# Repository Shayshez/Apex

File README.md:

# Apex
## CC-BY-SA 4.0
Rotatable Envelope/LFO/tap LFO/Drum generator, Based on MI "Peaks"

## ROTATABLE = Modules for 3u / 1u
Apex comes with 2 panels: 1u/20hp and 3u/6hp

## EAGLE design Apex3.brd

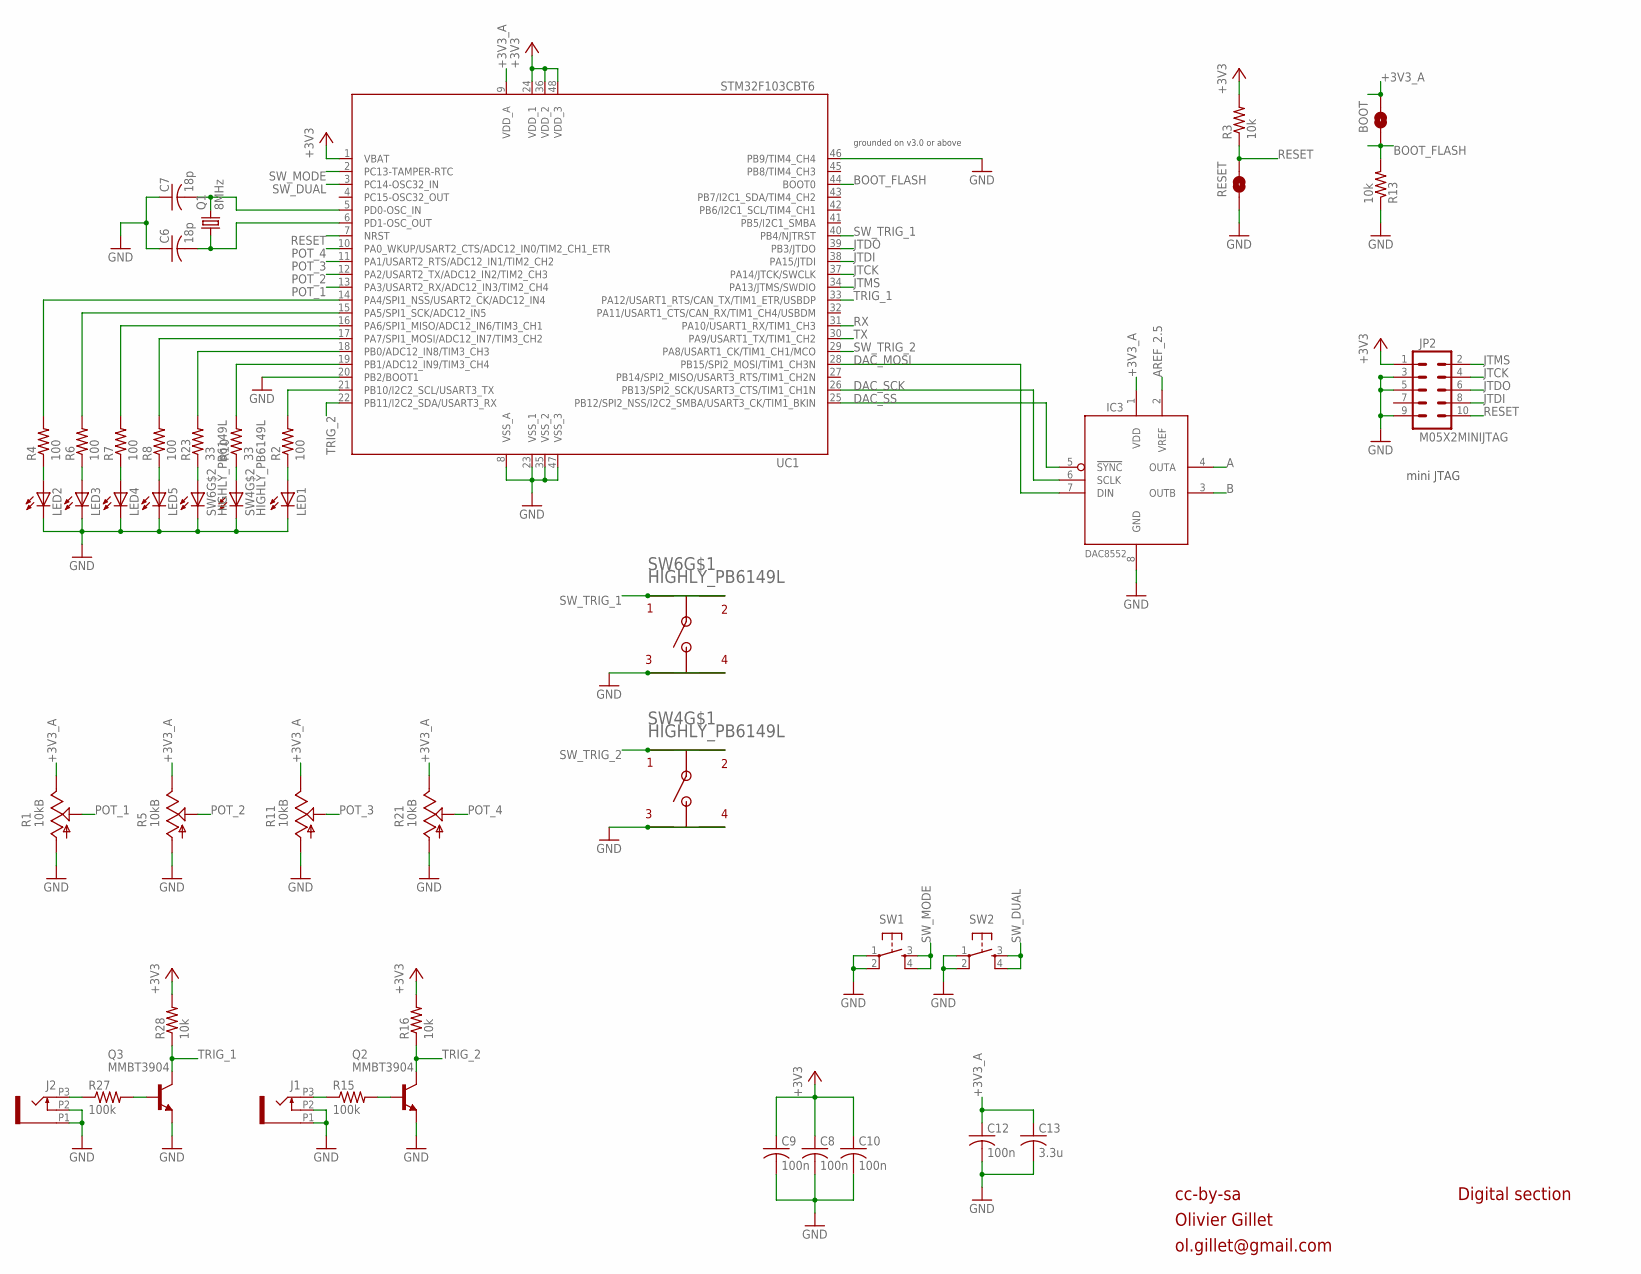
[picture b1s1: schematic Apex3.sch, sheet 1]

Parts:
BOOT: BOOT; SMT-JUMPER_2_NO_SILK
C6, C7: 18p; C0603
C8, C9, C10, C12: 100n; C0603
C13: 3.3u; C0603
IC3: DAC8552; MSOP-8
J1, J2: OG-PJ301_PJ301_THONKICONN; OG-PJ301_WQP_PJ_301M6_NO_HOLE
JP2: M05X2MINIJTAG; 2X5-1.27
LED1, LED2, LED3, LED4, LED5: LED3MM
Q1: 8MHz; HC49UP
Q2, Q3: MMBT3904; SOT23-BEC
R1, R5, R11, R21: 10kB; POT-ALPS_ALPS_POT_VERTICAL
R2, R4, R6, R7, R8: 100; R0603
R3, R13, R16, R28: 10k; R0603
R10, R23: 33; R0603
R15, R27: 100k; R0603
RESET: RESET; SMT-JUMPER_2_NO_SILK
SW1, SW2: TAC_SWITCHPTH; TACTILE-PTH
SW4, SW6: HIGHLY_PB6149L; HIGHLY_PB64149L
UC1: STM32F103CBT6; LQFP48

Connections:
+3V3: C8.1, C9.1, C10.1, JP2.1, R3.2, R16.2, R28.2, UC1.1 (VBAT), UC1.24 (VDD_1), UC1.36 (VDD_2), UC1.48 (VDD_3); also elsewhere on the board
+3V3_A: BOOT.2, C12.1, C13.1, IC3.1 (VDD), R1.P$1 (E), R5.P$1 (E), R11.P$1 (E), R21.P$1 (E), UC1.9 (VDD_A); also elsewhere on the board
A: IC3.4 (OUTA); also elsewhere on the board
AREF_2.5: IC3.2 (VREF); also elsewhere on the board
B: IC3.3 (OUTB); also elsewhere on the board
BOOT_FLASH: BOOT.1, R13.2, UC1.44 (BOOT0)
DAC_MOSI: IC3.7 (DIN), UC1.28 (PB15/SPI2_MOSI/TIM1_CH3N)
DAC_SCK: IC3.6 (SCLK), UC1.26 (PB13/SPI2_SCK/USART3_CTS/TIM1_CH1N)
DAC_SS: IC3.5 (!SYNC), UC1.25 (PB12/SPI2_NSS/I2C2_SMBA/USART3_CK/TIM1_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)
GND: C6.1, C7.1, C8.2, C9.2, C10.2, C12.2, C13.2, IC3.8 (GND), J1.P1 (1), J1.P2 (2), J2.P1 (1), J2.P2 (2), JP2.3, JP2.5, JP2.9, LED1.K (C), LED2.K (C), LED3.K (C), LED4.K (C), LED5.K (C), Q2.E, Q3.E, R1.P$3 (A), R5.P$3 (A), R11.P$3 (A), R13.1, R21.P$3 (A), RESET.1, SW1.1, SW1.2, SW2.1, SW2.2, SW4.L2, SW4.P$3, SW4.P$4, SW6.L2, SW6.P$3, SW6.P$4, UC1.8 (VSS_A), UC1.20 (PB2/BOOT1), UC1.23 (VSS_1), UC1.35 (VSS_2), UC1.46 (PB9/TIM4_CH4), UC1.47 (VSS_3); also elsewhere on the board
JTCK: JP2.4, UC1.37 (PA14/JTCK/SWCLK)
JTDI: JP2.8, UC1.38 (PA15/JTDI)
JTDO: JP2.6, UC1.39 (PB3/JTDO)
JTMS: JP2.2, UC1.34 (PA13/JTMS/SWDIO)
unnamed: J1.P3 (3), R15.1
unnamed: R23.2, UC1.18 (PB0/ADC12_IN8/TIM3_CH3)
unnamed: LED2.A, R4.1
unnamed: LED3.A, R6.1
unnamed: LED4.A, R7.1
unnamed: LED5.A, R8.1
unnamed: C7.2, Q1.2, UC1.5 (PD0-OSC_IN)
unnamed: C6.2, Q1.1, UC1.6 (PD1-OSC_OUT)
unnamed: R10.2, UC1.19 (PB1/ADC12_IN9/TIM3_CH4)
unnamed: R4.2, UC1.14 (PA4/SPI1_NSS/USART2_CK/ADC12_IN4)
unnamed: R6.2, UC1.15 (PA5/SPI1_SCK/ADC12_IN5)
unnamed: R7.2, UC1.16 (PA6/SPI1_MISO/ADC12_IN6/TIM3_CH1)
unnamed: R8.2, UC1.17 (PA7/SPI1_MOSI/ADC12_IN7/TIM3_CH2)
unnamed: Q2.B, R15.2
unnamed: R23.1, SW6.L1
unnamed: R10.1, SW4.L1
unnamed: LED1.A, R2.1
unnamed: R2.2, UC1.21 (PB10/I2C2_SCL/USART3_TX)
unnamed: J2.P3 (3), R27.1
unnamed: Q3.B, R27.2
POT_1: R1.P$2 (S), UC1.13 (PA3/USART2_RX/ADC12_IN3/TIM2_CH4)
POT_2: R5.P$2 (S), UC1.12 (PA2/USART2_TX/ADC12_IN2/TIM2_CH3)
POT_3: R11.P$2 (S), UC1.11 (PA1/USART2_RTS/ADC12_IN1/TIM2_CH2)
POT_4: R21.P$2 (S), UC1.10 (PA0_WKUP/USART2_CTS/ADC12_IN0/TIM2_CH1_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)
RESET: JP2.10, R3.1, RESET.2, UC1.7 (NRST)
RX: UC1.31 (PA10/USART1_RX/TIM1_CH3)
SW_DUAL: SW2.3, SW2.4, UC1.3 (PC14-OSC32_IN)
SW_MODE: SW1.3, SW1.4, UC1.2 (PC13-TAMPER-RTC)
SW_TRIG_1: SW6.P$1, SW6.P$2, UC1.40 (PB4/NJTRST)
SW_TRIG_2: SW4.P$1, SW4.P$2, UC1.29 (PA8/USART1_CK/TIM1_CH1/MCO)
TRIG_1: Q3.C, R28.1, UC1.33 (PA12/USART1_RTS/CAN_TX/TIM1_ETR/USBDP)
TRIG_2: Q2.C, R16.1, UC1.22 (PB11/I2C2_SDA/USART3_RX)
TX: UC1.30 (PA9/USART1_TX/TIM1_CH2)

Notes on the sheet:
cc-by-sa
Olivier Gillet
ol.gillet@gmail.com
Digital section
mini JTAG
grounded on v3.0 or above

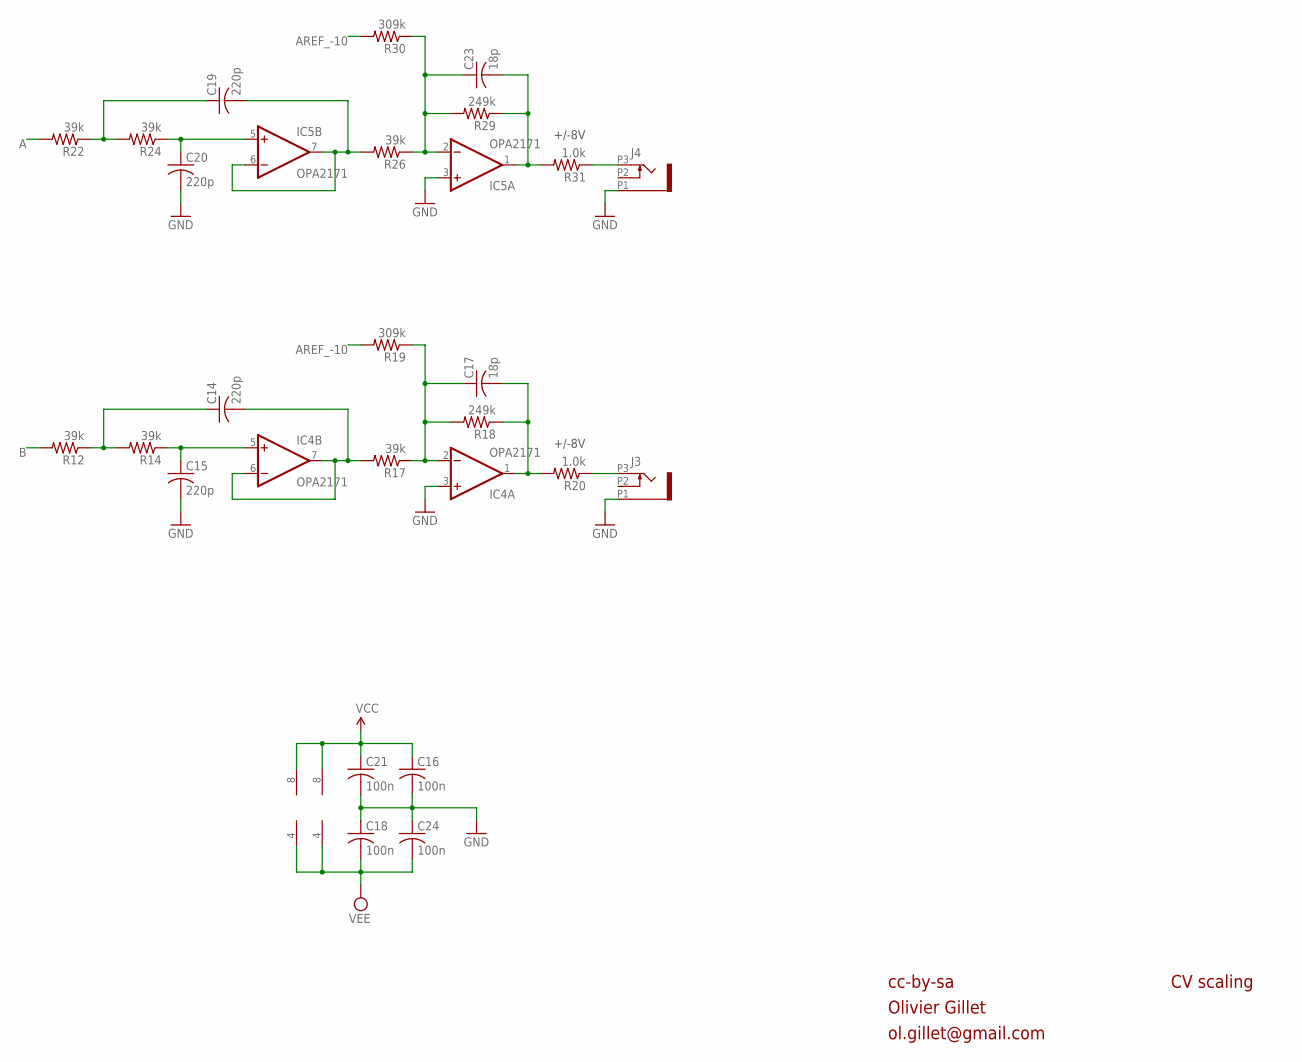
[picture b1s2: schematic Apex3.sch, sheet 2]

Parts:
C14, C15, C19, C20: 220p; C0603
C16, C18, C21, C24: 100n; C0603
C17, C23: 18p; C0603
IC4, IC5: OPA2171; SO08
J3, J4: OG-PJ301_PJ301_THONKICONN; OG-PJ301_WQP_PJ_301M6_NO_HOLE
R12, R14, R17, R22, R24, R26: 39k; R0603
R18, R29: 249k; R0603
R19, R30: 309k; R0603
R20, R31: 1.0k; R0603

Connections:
A: R22.2; also elsewhere on the board
AREF_-10: R19.2, R30.2; also elsewhere on the board
B: R12.2; also elsewhere on the board
BI_OUT: C17.2, IC4.1 (OUT), R18.1, R20.2
BI_OUT1: C23.2, IC5.1 (OUT), R29.1, R31.2
F_CV: C17.1, IC4.2 (-IN), R17.1, R18.2, R19.1
F_CV1: C23.1, IC5.2 (-IN), R26.1, R29.2, R30.1
GND: C15.2, C16.2, C18.1, C20.2, C21.2, C24.1, IC4.3 (+IN), IC5.3 (+IN), J3.P1 (1), J4.P1 (1); also elsewhere on the board
unnamed: C19.2, IC5.6 (-IN), IC5.7 (OUT), R26.2
unnamed: C20.1, IC5.5 (+IN), R24.1
unnamed: C19.1, R22.1, R24.2
unnamed: J3.P3 (3), R20.1
unnamed: J4.P3 (3), R31.1
unnamed: C14.2, IC4.6 (-IN), IC4.7 (OUT), R17.2
unnamed: C15.1, IC4.5 (+IN), R14.1
unnamed: C14.1, R12.1, R14.2
VCC: C16.1, C21.1, IC4.8 (V+), IC5.8 (V+); also elsewhere on the board
VEE: C18.2, C24.2, IC4.4 (V-), IC5.4 (V-); also elsewhere on the board

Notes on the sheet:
+/-8V
cc-by-sa
Olivier Gillet
ol.gillet@gmail.com
CV scaling

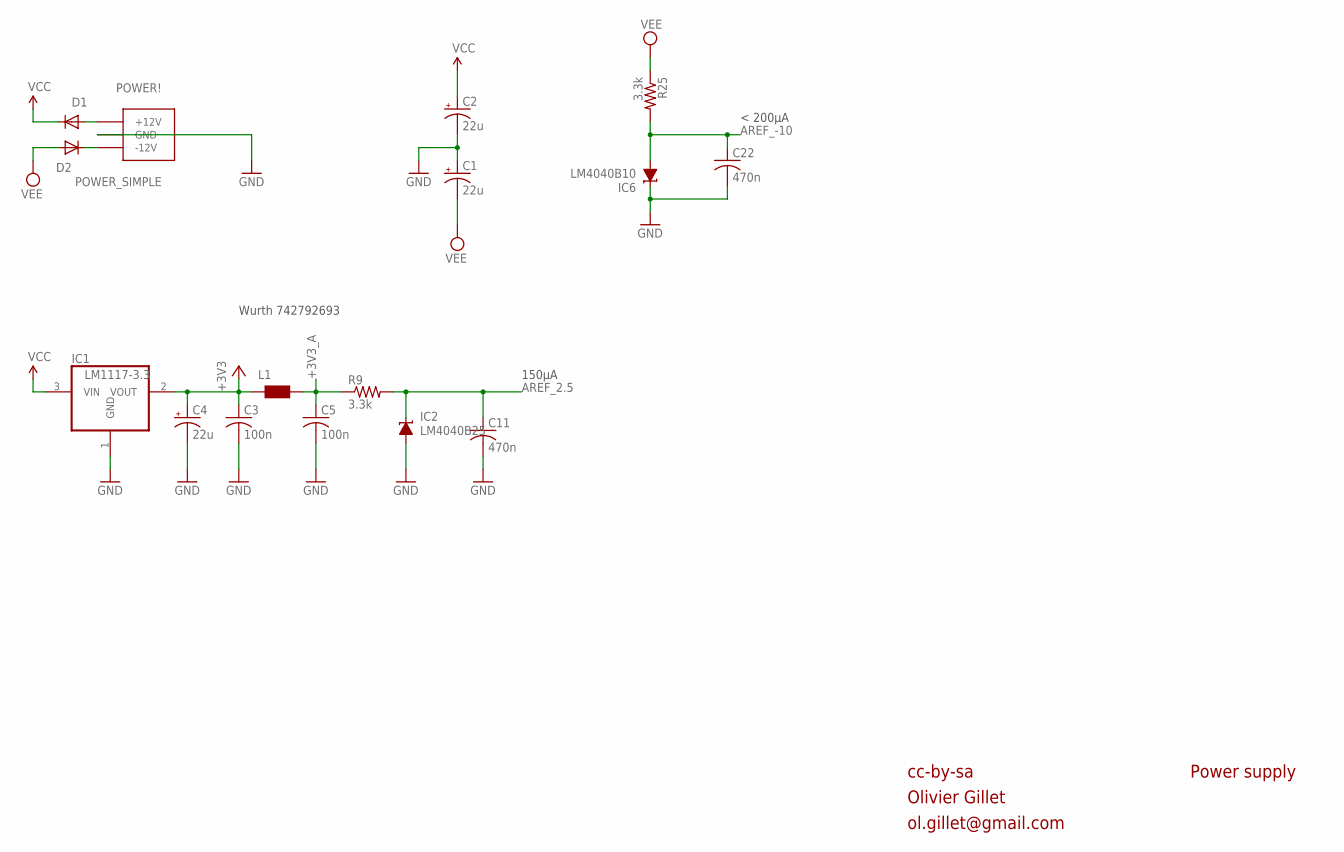
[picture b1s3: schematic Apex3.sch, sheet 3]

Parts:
C1, C2, C4: 22u; PANASONIC_C
C3, C5: 100n; C0603
C11, C22: 470n; C0603
D1, D2: 1N5819HW; SOD123
IC1: LM1117-3.3; SOT223
IC2: LM4040B25; DBZ_R-PDSO-G3
IC6: LM4040B10; DBZ_R-PDSO-G3
L1: WE-CBF_0603; 0603
POWER!: POWER_SIMPLE; 2X05_SMT_HEADER
R9, R25: 3.3k; R0603

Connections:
+3V3: C3.1, C4.+, IC1.2 (VOUT), L1.1; also elsewhere on the board
+3V3_A: C5.1, L1.2, R9.1; also elsewhere on the board
AREF_2.5: C11.1, IC2.1 (C), R9.2; also elsewhere on the board
AREF_-10: C22.1, IC6.2 (A), R25.2; also elsewhere on the board
GND: C1.+, C2.-, C3.2, C4.-, C5.2, C11.2, C22.2, IC1.1 (GND), IC2.2 (A), IC6.1 (C), POWER!.3 (GND), POWER!.4 (GND), POWER!.5 (GND), POWER!.6 (GND), POWER!.7 (GND), POWER!.8 (GND); also elsewhere on the board
unnamed: D1.A, POWER!.9 (+12V), POWER!.10 (+12V)
unnamed: D2.C, POWER!.1 (-12V), POWER!.2 (-12V)
VCC: C2.+, D1.C, IC1.3 (VIN); also elsewhere on the board
VEE: C1.-, D2.A, R25.1; also elsewhere on the board

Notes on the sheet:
cc-by-sa
Olivier Gillet
ol.gillet@gmail.com
Power supply
Wurth 742792693
< 200µA
150µA

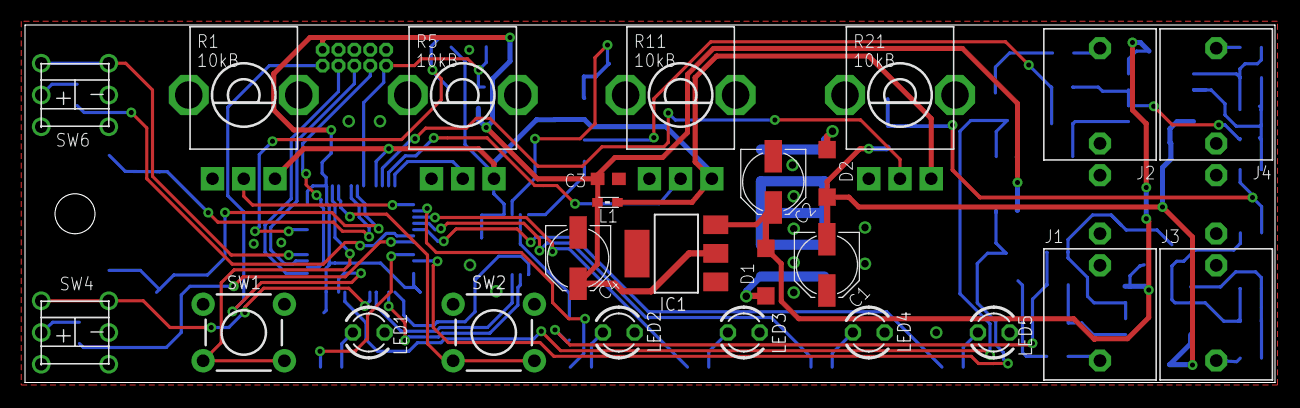
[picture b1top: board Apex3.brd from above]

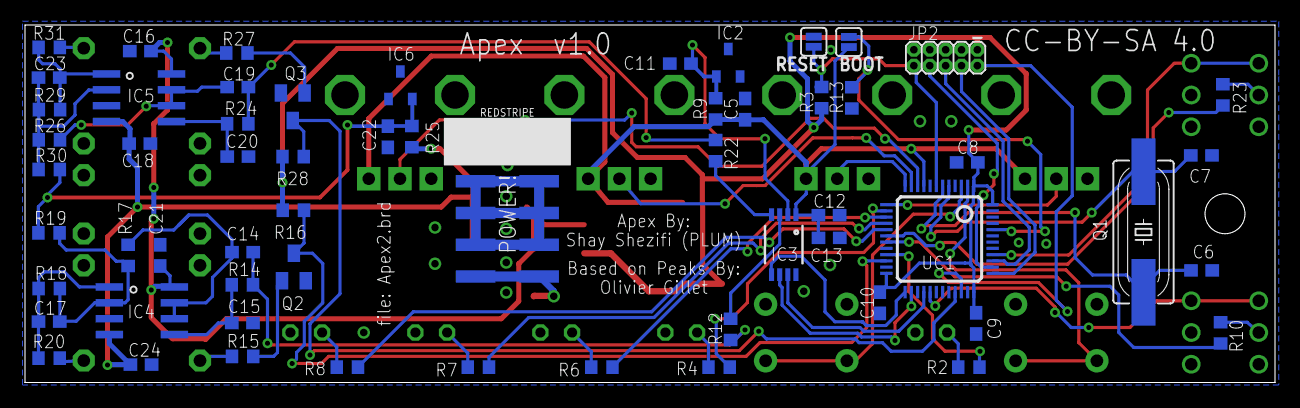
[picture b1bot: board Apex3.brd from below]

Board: 2 copper layers, 100.0 x 28.6 mm, 85 parts (60 on the bottom side), 62 nets.

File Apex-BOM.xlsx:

Qty | Value | Device | Package | Parts | Description
2 | 33 | R-US_R0603 | R0603 | R10, R23 | RESISTOR, American symbol
5 | 100 | R-US_R0603 | R0603 | R2, R4, R6, R7, R8 | RESISTOR, American symbol
2 | 1.0k | R-US_R0603 | R0603 | R20, R31 | RESISTOR, American symbol
2 | 3.3k | R-US_R0603 | R0603 | R9, R25 | RESISTOR, American symbol
4 | 10k | R-US_R0603 | R0603 | R3, R13, R16, R28 | RESISTOR, American symbol
2 | 100k | R-US_R0603 | R0603 | R15, R27 | RESISTOR, American symbol
6 | 39k | R-US_R0603 | R0603 | R12, R14, R17, R22, R24, R26 | RESISTOR, American symbol
2 | 249k | R-US_R0603 | R0603 | R18, R29 | RESISTOR, American symbol
2 | 309k | R-US_R0603 | R0603 | R19, R30 | RESISTOR, American symbol
4 | 18p | C-USC0603 | C0603 | C6, C7, C17, C23 | CAPACITOR, American symbol
4 | 220p | C-USC0603 | C0603 | C14, C15, C19, C20 | CAPACITOR, American symbol
10 | 100n | C-USC0603 | C0603 | C3, C5, C8, C9, C10, C12, C16, C18, C21, C24 | CAPACITOR, American symbol
2 | 470n | C-USC0603 | C0603 | C11, C22 | CAPACITOR, American symbol
1 | 3.3u | C-USC0603 | C0603 | C13 | CAPACITOR, American symbol
3 | 22u | CPOL-USC | PANASONIC_C | C1, C2, C4 | POLARIZED CAPACITOR, American symbol
1 |  | WE-CBF_0603 | 603 | L1 | SMD EMI Suppression Ferrite Beads
2 | 1N5819HW | DIODE-SOD123 | SOD123 | D1, D2 | DIODE
1 | LM4040B10 | LM4041B12DBZ | DBZ_R-PDSO-G3 | IC6 | PRECISION MICROPOWER SHUNT VOLTAGE REFERENCE
1 | LM4040B25 | LM4041B12DBZ | DBZ_R-PDSO-G3 | IC2 | PRECISION MICROPOWER SHUNT VOLTAGE REFERENCE
1 | 8MHz | CRYSTALHC49UP | HC49UP | Q1 | CRYSTAL
2 | HIGHLY_PB6149L | HIGHLY_PB6149L | HIGHLY_PB64149L | SW4, SW6
1 | STM32F103CBT6 | STM32F103CB | LQFP48 | UC1
1 | DAC8552 | DAC8552 | MSOP-8 | IC3
2 | OPA2171 | TL072D | SO08 | IC4, IC5 | OP AMP
1 | LM1117-3.3 | REG1117 | SOT223 | IC1 | 800mA and 1A Low Dropout (LDO) Positive Regulator
2 | MMBT3904 | MMBT3904LT1-NPN-SOT23-BEC | SOT23-BEC | Q2, Q3 | NPN Transistror
2 |  | TAC_SWITCHPTH | TACTILE-PTH | SW1, SW2 | Momentary Switch
4 | 10kB | POT_USVERTICAL_PS | ALPS_POT_VERTICAL_PS | R1, R5, R11, R21
4 | OG-PJ301_PJ301_THONKICONN | OG-PJ301_PJ301_THONKICONN | OG-PJ301_WQP_PJ_301M6_NO_HOLE | J1, J2, J3, J4
5 |  | LED3MM | LED3MM | LED1, LED2, LED3, LED4, LED5 | LED
1 | M05X2MINIJTAG | M05X2MINIJTAG | 2X5-1.27 | JP2 | Header 5x2
1 | POWER_SIMPLE | POWER_SIMPLE | 2X05_SMT_HEADER | POWER!

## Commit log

2019-02-05 Rename Firmware/DMC + Calobration/peaks_DMC_with_calibn.hex to Firmware/DMC+Calibrtion/peaks_DMC_with_calibn.hex
2019-02-05 Rename Firmware/DMC + Calobration/peaks_bootloader_DMC_with_calibn.hex to Firmware/DMC + Calibration/peaks_bootloader_DMC_with_calibn.hex
2019-02-05 Rename Firmware/DMC + Calibration/peaks_bootloader_DMC_with_calibn.hex to Firmware/DMC+Calibration/peaks_bootloader_DMC_with_calibn.hex

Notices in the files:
parts and their libraries:
SparkFun-Jumpers: Licensing: Creative Commons ShareAlike 4.0 International - https://creativecommons.org/licenses/by-sa/4.0
